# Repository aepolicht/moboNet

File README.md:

moboNet
=======

  This repo is a collection of elements contributing to one home automation project. It consists of analysis, schematics,
and software.

Notes
=====

Version 0.0.1
	Added Features:
		-Recall previous state from memory using EEPROM

	Bug Fixes:
		-Remove Flashes when receiving message

Version 0.0.2
	Added Features:
		-All communication now shall be over UDP packets

Version 0.0.3
	Changes:
		-Added notifications features to all devices
		-Added basic music detection and visualization code
			-Changes were also made to the hardware side of the music detection.
			 The low pass filter desired seems to have a cutoff right at 220 Hz.
		 	 Ideally this simple filter will consist of a 1 uF capacitor and a
		 	 7.5 kOhm resistor.
		-Implemented serial connection to bulb array to communicate with display 
		 projection from PC. Currently it checks serial, then homenet for any input
		 but if this proves to slow down the projection too much i may need a blocking
		 version where when serial is inbound all other code is ignored.
		-Changed to "FastSPI" library for communication with WS2801 LED strings
			-Also tried out an Adafruit library for this purpose but i found that
			 that library was blocking and took significantly more time to run
			 than the FastSPI library took.
			-FastSPI is non-blocking and takes around 300 uS to finish its write
		     otherwise overwriting while in progress produces undesirable effects.
	    -Implemented notifications for door knock however the whole system needs an
	     overhaul to simplify the process of [alarm device]->[base station]->[bulb clients]
	    -Implemented code for the door knock detector notifier.
	    
Version 0.0.4
	Note:
		I have begun to implement the music detection system. The basis for the whole system
		is contingent upon the frequency response of the low pass filter. I have chosen a simple
		filter with passband edge around 300 Hz. In this design a large gap between the passband 
		and the stop-band is desired because of how i plan to implement the software side of the
		music detection. Here is a rough graph of the frequency response:

			                    |H(w)| for LPF (1st order fc = 300Hz)
					  (dB)
					 0	|x x x x x x x x x x x 
					 	|                      x 
					-5	|                        x 
						|                          x
					-10	|                            x
						|                              x              
					-15	|                                x               
						|                                  x         
					-20	|                                    x           
						|                                      x         
					-25	|                                        x            
						|                                          x              
					-30	|                                            x                  
						|                                              x      
					-35	|                                                x      
						-------|----------|-----------|------------|----- Hz (log)
						0     10         100        1000         10000   

		The basis for the software side is having an understanding of the filters response
		and using this to determine whether or not the input signal is a Low, Mid or High.
		I am doing it this way to avoid any additional circuitry because i want a small
		package. It is easiest to detect the beat and very low frequencies because these are
		the largest in magnitude. I want a large gap between the passband and stop-band edges
		because i want to be able to detect other frequencies at attenuated magnitudes.
		To overcome the problem of detecting loud mids as a bass and other situations, i take
		an average of the last 64 samples as a reference. Given that reference the respective
		frequencies will then be function of the average unique to those frequency bands. To
		obtain a reference i sampled the desired frequency at different volumes IE different 
		values of the variable "ave". I then applied best fit lines and use them as cutoffs
		to determine which band a sample should be classified to. The best fits i have found
		are:
 
			Lows  (0-230Hz)   Threshold = 67*log(ave-1)-10
			Mids  (230-800Hz) Threshold = 25*log(ave-1)-5
			Highs (800+Hz)    Threshold = 12*log(ave-1)-5

		It is much more difficult to detect a high with this filter because signals higher than 
		800 Hz are attenuated more severely beginning with 800 Hz at -9 dB. The other method for
		doing this type of thing would be with a ~6000 Hz lpf and performing an FFT which i will
		do to see if its viable given the constraints.

		My preliminary DFT implementation with a 128 sample input and no special windowing takes around 2.5 seconds per DFT which is much too long. When N is 32, it takes about 155 mS.
		This would mean a sampling rate of T > 155 mS which a sampling frequency of less than
		6 Hz which is pretty much useless. The to attain a Nyquist frequency of a signal of 2000 Hz
		i need to have a sampling frequency of 4000 Hz which means the DFT finish in <250 uS. I 
		have found an FFT library for Arduino but it takes more than 600 uS to complete the FFT.
		This means i will continue with my previous method of implementing the lump spectral
		analysis.

TBD:
x-Add days support to android
x-Redesign notifications so that they are handled by base station
o-Setup music mode on all devices
x-Setup Door knock codes for base station and knocker
o-Setup Ambiance mode
o-Fix Android save and return functionality
o-Finish C# desktop application
o-Add notification options to base station and android options menu
o-Implement Groups on all devices

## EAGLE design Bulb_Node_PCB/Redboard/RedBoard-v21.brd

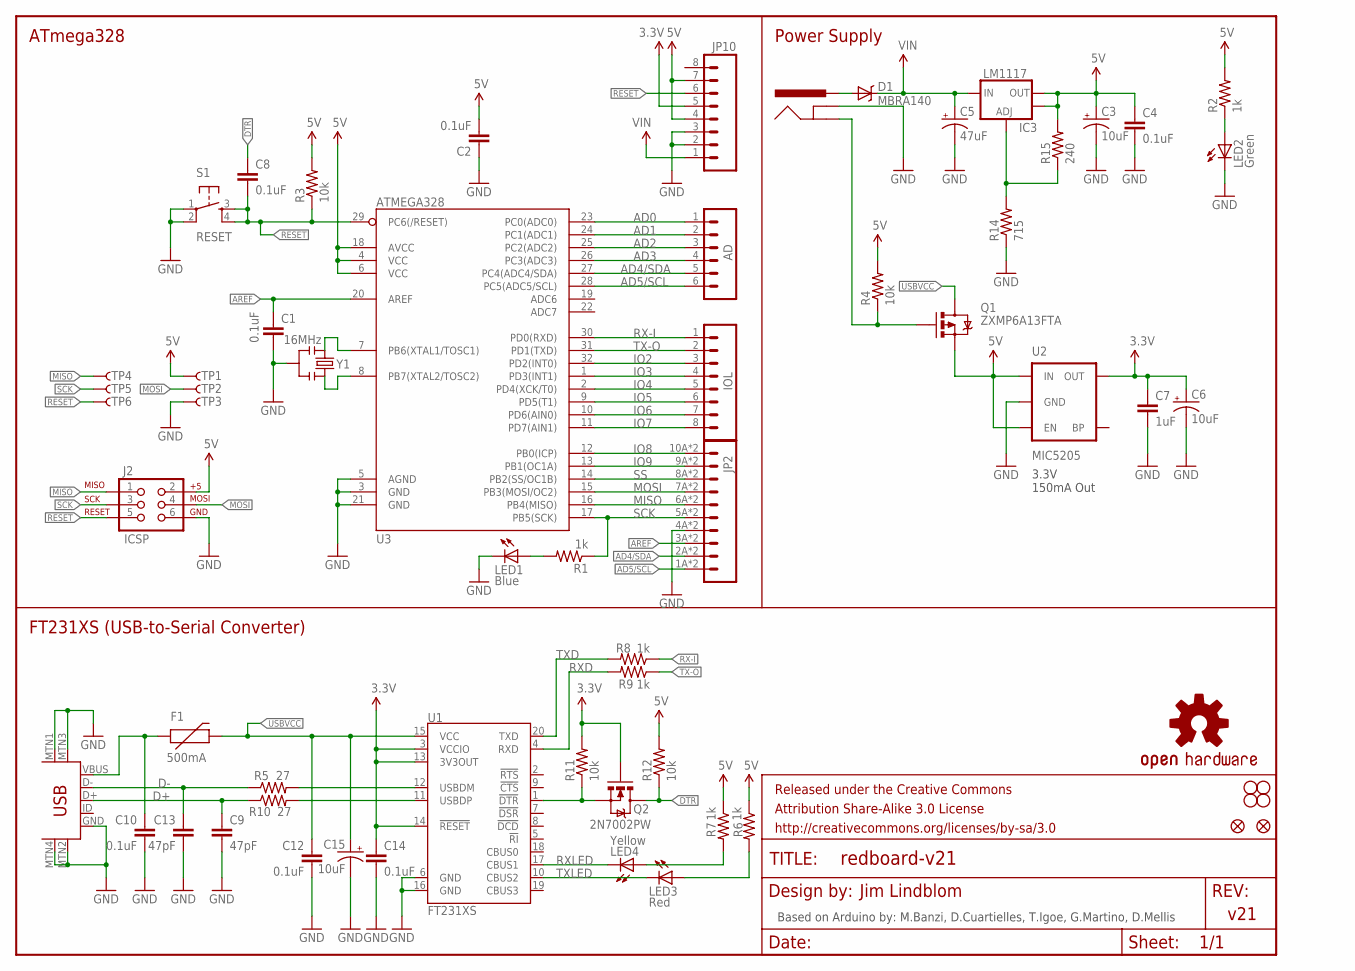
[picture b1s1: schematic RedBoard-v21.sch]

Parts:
AD: M06SMD-STRAIGHT-COMBO; 1X06_SMD_STRAIGHT_COMBO
C1, C2, C4, C8, C10, C12, C14: 0.1uF; 0603-CAP
C3, C6, C15: 10uF; EIA3216
C5: 47uF; PANASONIC_D
C7: 1uF; 0603-CAP
C9, C13: 47pF; 0603-CAP
D1: MBRA140; SMA-DIODE
F1: 500mA; PTC-1206
FRAME2: FRAME-LETTER; CREATIVE_COMMONS
IC3: LM1117; SOT223-ALT1
IOL: M08SMD-COMBO; 1X08_SMD_COMBINED
J1: POWER_JACKOVERPASTE_REDBOARD_0603; POWER_JACK_SMD_OVERPASTE_REDBOARD_0603
J2: ICSP; 2X3_SMT_POSTS
JP2: M10SMD_COMBO; 1X10_SMD_COMBINED
JP3, JP4, JP5, JP6: STAND-OFF
JP8, JP9: FIDUCIAL1X2; FIDUCIAL-1X2
JP10: M08SMD-COMBO; 1X08_SMD_COMBINED
LED1: Blue; LED-1206-NO_SILK
LED2: Green; LED-1206-NO_SILK
LED3: Red; LED-1206-NO_SILK
LED4: Yellow; LED-1206-NO_SILK
Q1: ZXMP6A13FTA; SOT23-3
Q2: 2N7002PW; SOT323
R1, R2, R6, R7, R8, R9: 1k; 0603-RES
R3, R4, R11, R12: 10k; 0603-RES
R5, R10: 27; 0603-RES
R14: 715; 0603-RES
R15: 240; 0603-RES
S1: RESET; TACTILE_SWITCH_SMD
TP1, TP2, TP3, TP4, TP5, TP6: TP-3x5; PAD.03X.05
U1: FT231XS; SSOP20_L
U2: MIC5205; SOT23-5
U3: ATMEGA328; TQFP32-08
U$13: USB-MINIB-5PIN; USB-MINIB
U$16: OSHW-LOGOS; OSHW-LOGO-S
Y1: 16MHz; RESONATOR-SMD

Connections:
3.3V: C6.A (+), C7.1, C14.1, JP10.5, Q2.1 (G), R11.2, U1.3 (VCCIO), U1.13 (3V3OUT), U1.14 (!RESET), U2.5 (OUT)
5V: C2.2, C3.A (+), C4.1, IC3.2 (OUT), IC3.4 (OUT), J2.2, JP10.4, JP10.7, Q1.2 (S), R2.2, R3.2, R4.2, R6.1, R7.1, R12.2, R15.2, TP1.P$1, U2.1 (IN), U2.3 (EN), U3.4 (VCC), U3.6 (VCC), U3.18 (AVCC)
AD0: AD.1, U3.23 (PC0(ADC0))
AD1: AD.2, U3.24 (PC1(ADC1))
AD2: AD.3, U3.25 (PC2(ADC2))
AD3: AD.4, U3.26 (PC3(ADC3))
AD4/SDA: AD.5, JP2.2A (2), JP2.2B (2), U3.27 (PC4(ADC4/SDA))
AD5/SCL: AD.6, JP2.1A (1), JP2.1B (1), U3.28 (PC5(ADC5/SCL))
AREF: C1.1, JP2.3A (3), JP2.3B (3), U3.20 (AREF)
D+: C9.1, R10.1, U$13.D+
D-: C13.1, R5.1, U$13.D-
DTR: C8.1, Q2.3 (D), R12.1
GND: C1.2, C2.1, C3.C (-), C4.2, C5.-, C6.C (-), C7.2, C9.2, C10.2, C12.2, C13.2, C14.2, C15.C (-), J1.GND (GNDBREAK), J2.6, JP2.4A (4), JP2.4B (4), JP10.2, JP10.3, LED1.C, LED2.C, R14.1, S1.1, S1.2, TP3.P$1, U1.6 (GND), U1.16 (GND), U2.2 (GND), U3.3 (GND), U3.5 (AGND), U3.21 (GND), U$13.GND, U$13.MTN1 (MTN2), U$13.MTN2 (MTN3), U$13.MTN3 (MTN1), U$13.MTN4, Y1.2
INSERT: J1.P$4 (GND), Q1.1 (G), R4.1
IO2: IOL.3, U3.32 (PD2(INT0))
IO3: IOL.4, U3.1 (PD3(INT1))
IO4: IOL.5, U3.2 (PD4(XCK/T0))
IO5: IOL.6, U3.9 (PD5(T1))
IO6: IOL.7, U3.10 (PD6(AIN0))
IO7: IOL.8, U3.11 (PD7(AIN1))
IO8: JP2.10A (10), JP2.10B (10), U3.12 (PB0(ICP))
IO9: JP2.9A (9), JP2.9B (9), U3.13 (PB1(OC1A))
MISO: J2.1, JP2.6A (6), JP2.6B (6), TP4.P$1, U3.16 (PB4(MISO))
MOSI: J2.4, JP2.7A (7), JP2.7B (7), TP2.P$1, U3.15 (PB3(MOSI/OC2))
unnamed: LED1.A, R1.2
unnamed: LED2.A, R2.1
unnamed: U3.7 (PB6(XTAL1/TOSC1)), Y1.1
unnamed: U3.8 (PB7(XTAL2/TOSC2)), Y1.3
unnamed: R5.2, U1.12 (USBDM)
unnamed: R10.2, U1.11 (USBDP)
unnamed: LED3.A, R6.2
unnamed: LED4.A, R7.2
unnamed: Q2.2 (S), R11.1, U1.1 (!DTR)
unnamed: IC3.1 (ADJ), R14.2, R15.1
PWRIN: D1.A, J1.VIN0 (PWR)
RESET: C8.2, J2.5, JP10.6, R3.1, S1.3, S1.4, TP6.P$1, U3.29 (PC6(/RESET))
RX-I: IOL.1, R8.1, U3.30 (PD0(RXD))
RXD: R9.2, U1.4 (RXD)
RXLED: LED4.C, U1.17 (CBUS1)
SCK: J2.3, JP2.5A (5), JP2.5B (5), R1.1, TP5.P$1, U3.17 (PB5(SCK))
SS: JP2.8A (8), JP2.8B (8), U3.14 (PB2(SS/OC1B))
TX-O: IOL.2, R9.1, U3.31 (PD1(TXD))
TXD: R8.2, U1.20 (TXD)
TXLED: LED3.C, U1.10 (CBUS2)
USBVCC: C12.1, C15.A (+), F1.2, Q1.3 (D), U1.15 (VCC)
VIN: C5.+, D1.C, IC3.3 (IN), JP10.1
VUSB: C10.1, F1.1, U$13.VBUS

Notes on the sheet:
Power Supply
ATmega328
FT231XS (USB-to-Serial Converter)
Based on Arduino by: M.Banzi, D.Cuartielles, T.Igoe, G.Martino, D.Mellis
3.3V 150mA Out
Jim Lindblom
v21

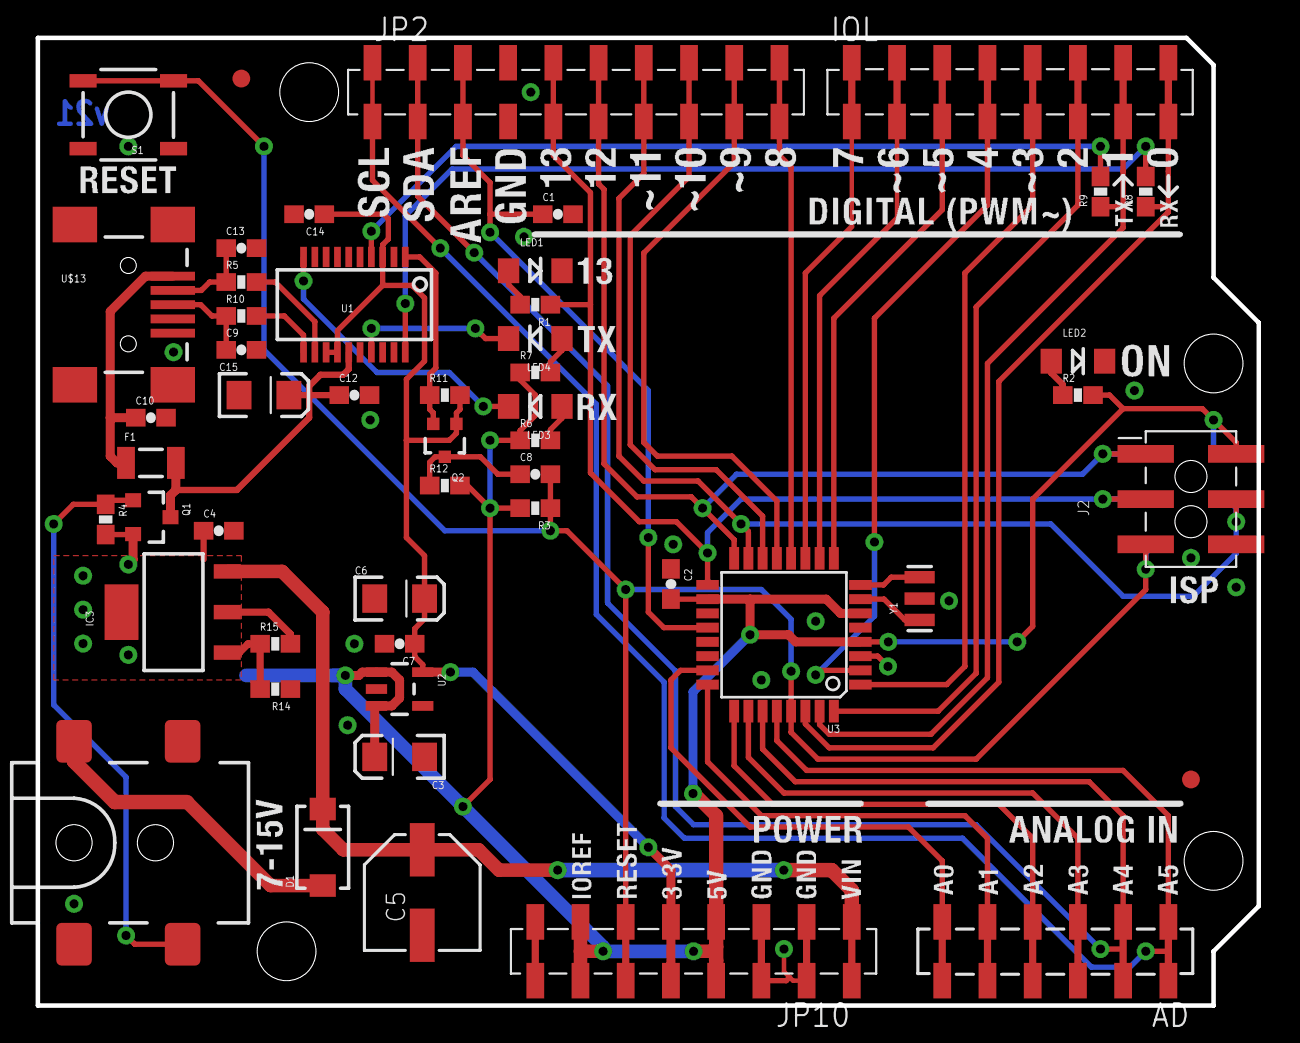
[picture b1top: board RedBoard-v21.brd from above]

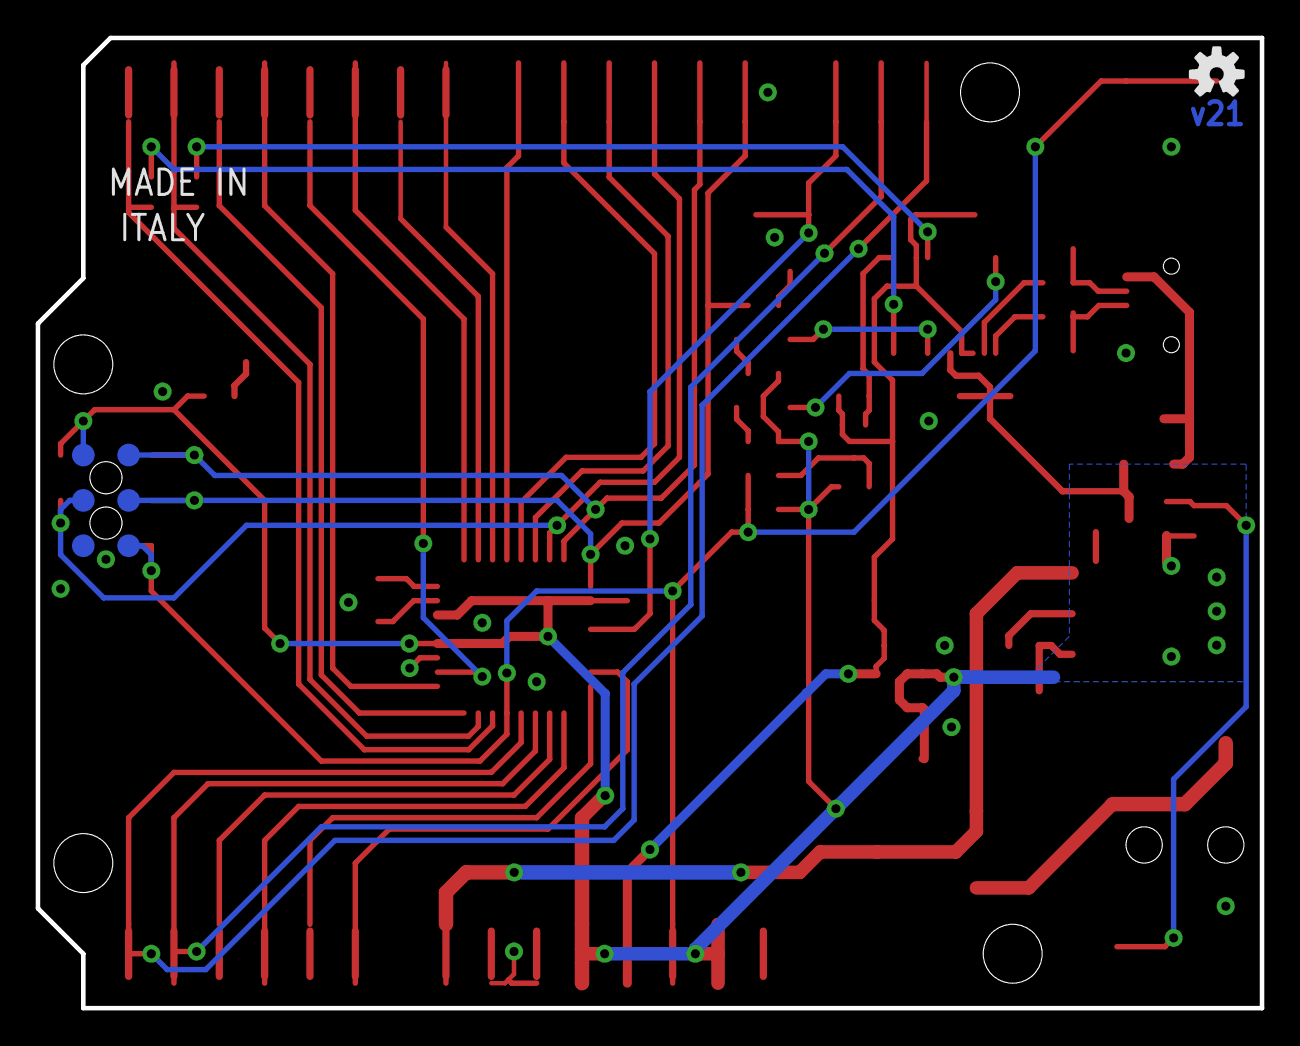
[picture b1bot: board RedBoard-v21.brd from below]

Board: 2 copper layers, 68.6 x 54.4 mm, 63 parts (7 on the bottom side), 47 nets.

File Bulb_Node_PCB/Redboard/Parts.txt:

Partlist

Exported from RedBoard-v21.sch at 2/24/2015 8:32:50 PM

EAGLE Version 7.1.0 Copyright (c) 1988-2014 CadSoft

Assembly variant: 

Part     Value                             Device                            Package                                Library               Sheet

AD                                         M06SMD-STRAIGHT-COMBO             1X06_SMD_STRAIGHT_COMBO                SparkFun              1
C1       0.1uF                             CAP0603-CAP                       0603-CAP                               SparkFun              1
C2       0.1uF                             CAP0603-CAP                       0603-CAP                               SparkFun              1
C3       10uF                              CAP_POL1206                       EIA3216                                SparkFun              1
C4       0.1uF                             CAP0603-CAP                       0603-CAP                               SparkFun              1
C5       47uF                              CAP_POLD                          PANASONIC_D                            SparkFun              1
C6       10uF                              CAP_POL1206                       EIA3216                                SparkFun              1
C7       1uF                               CAP0603-CAP                       0603-CAP                               SparkFun              1
C8       0.1uF                             CAP0603-CAP                       0603-CAP                               SparkFun              1
C9       47pF                              47PF-50V-5%(0603)                 0603-CAP                               SparkFun-Capacitors   1
C10      0.1uF                             CAP0603-CAP                       0603-CAP                               SparkFun              1
C12      0.1uF                             CAP0603-CAP                       0603-CAP                               SparkFun              1
C13      47pF                              47PF-50V-5%(0603)                 0603-CAP                               SparkFun-Capacitors   1
C14      0.1uF                             CAP0603-CAP                       0603-CAP                               SparkFun              1
C15      10uF                              CAP_POL1206                       EIA3216                                SparkFun-Capacitors   1
D1       MBRA140                           DIODE-SCHOTTKY_                   SMA-DIODE                              SparkFun              1
F1       500mA                             PTCSMD                            PTC-1206                               SparkFun              1
IC3      LM1117                            V_REG_LM1117ALT1                  SOT223-ALT1                            Testing               1
IOL                                        M08SMD-COMBO                      1X08_SMD_COMBINED                      SparkFun              1
J1       POWER_JACKOVERPASTE_REDBOARD_0603 POWER_JACKOVERPASTE_REDBOARD_0603 POWER_JACK_SMD_OVERPASTE_REDBOARD_0603 Testing               1
J2       ICSP                              AVR_SPI_PRG_6SMT_MALE             2X3_SMT_POSTS                          SparkFun-Connectors   1
JP2      M10SMD_COMBO                      M10SMD_COMBO                      1X10_SMD_COMBINED                      SparkFun-Connectors   1
JP10                                       M08SMD-COMBO                      1X08_SMD_COMBINED                      SparkFun-Connectors   1
LED1     Blue                              LED1206-NS                        LED-1206-NO_SILK                       SparkFun-LED          1
LED2     Green                             LED1206-NS                        LED-1206-NO_SILK                       SparkFun-LED          1
LED3     Red                               LED1206-NS                        LED-1206-NO_SILK                       SparkFun-LED          1
LED4     Yellow                            LED1206-NS                        LED-1206-NO_SILK                       SparkFun-LED          1
Q1       ZXMP6A13FTA                       MOSFET-PCHANNELSMD                SOT23-3                                SparkFun              1
Q2       2N7002PW                          MOSFET-NCHANNEL2N7002PW           SOT323                                 SparkFun-DiscreteSemi 1
R1       1k                                RESISTOR0603-RES                  0603-RES                               SparkFun              1
R2       1k                                RESISTOR0603-RES                  0603-RES                               SparkFun              1
R3       10k                               RESISTOR0603-RES                  0603-RES                               SparkFun              1
R4       10k                               RESISTOR0603-RES                  0603-RES                               SparkFun              1
R5       27                                RESISTOR0603-RES                  0603-RES                               SparkFun-Resistors    1
R6       1k                                RESISTOR0603-RES                  0603-RES                               SparkFun              1
R7       1k                                RESISTOR0603-RES                  0603-RES                               SparkFun              1
R8       1k                                RESISTOR0603-RES                  0603-RES                               SparkFun              1
R9       1k                                RESISTOR0603-RES                  0603-RES                               SparkFun              1
R10      27                                RESISTOR0603-RES                  0603-RES                               SparkFun-Resistors    1
R11      10k                               RESISTOR0603-RES                  0603-RES                               SparkFun              1
R12      10k                               RESISTOR0603-RES                  0603-RES                               SparkFun              1
R14      715                               RESISTOR0603-RES                  0603-RES                               SparkFun              1
R15      240                               RESISTOR0603-RES                  0603-RES                               SparkFun              1
S1       RESET                             TAC_SWITCHSMD                     TACTILE_SWITCH_SMD                     SparkFun              1
TP1      TP-3x5                            TEST-POINT3X5                     PAD.03X.05                             SparkFun-Passives     1
TP2      TP-3x5                            TEST-POINT3X5                     PAD.03X.05                             SparkFun-Passives     1
TP3      TP-3x5                            TEST-POINT3X5                     PAD.03X.05                             SparkFun-Passives     1
TP4      TP-3x5                            TEST-POINT3X5                     PAD.03X.05                             SparkFun-Passives     1
TP5      TP-3x5                            TEST-POINT3X5                     PAD.03X.05                             SparkFun-Passives     1
TP6      TP-3x5                            TEST-POINT3X5                     PAD.03X.05                             SparkFun-Passives     1
U$13     USB-MINIB-5PIN                    USB-MINIB-5PIN                    USB-MINIB                              SparkFun-Connectors   1
U1       FT231XS                           FT231XS                           SSOP20_L                               SparkFun-DigitalIC    1
U2       MIC5205                           V_REG_LDOSMD                      SOT23-5                                SparkFun              1
U3       ATMEGA328                         ATMEGA168                         TQFP32-08                              SparkFun              1
Y1       16MHz                             RESONATORSMD                      RESONATOR-SMD                          SparkFun-FreqCtrl     1

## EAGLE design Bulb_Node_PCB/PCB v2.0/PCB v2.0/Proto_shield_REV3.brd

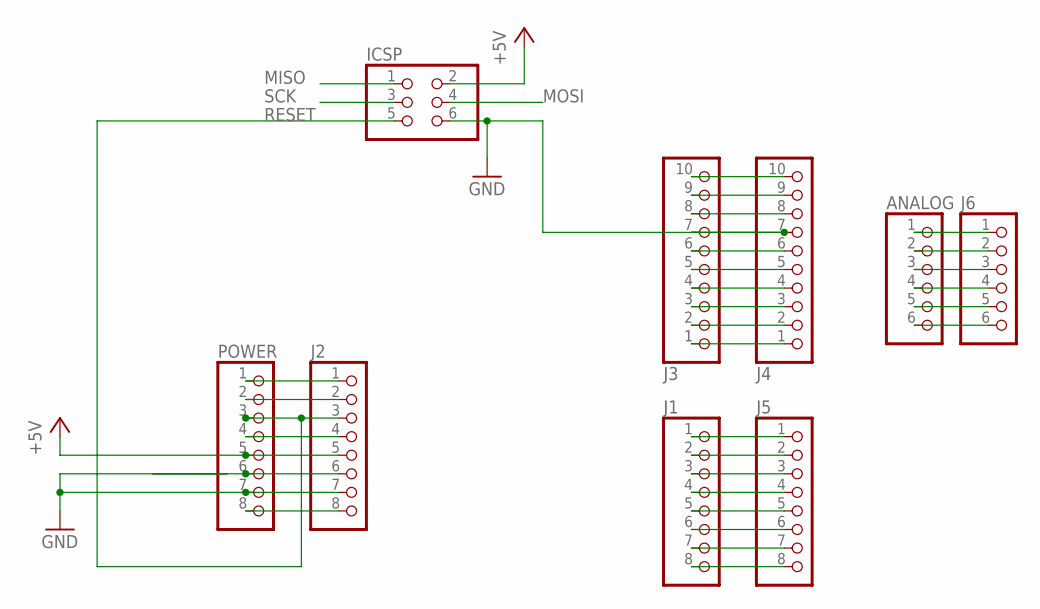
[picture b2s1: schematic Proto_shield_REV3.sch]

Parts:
ANALOG: PINHD-1X6; 1X06
ICSP: PINHD-2X3; 2X03
J1, J2, J5: PINHD-1X8TH; 1X08-TH
J3, J4: PINHD-1X10TH; 1X10-TH
J6: PINHD-1X6; 1X06
POWER: PINHD-1X8TH; 1X08-TH

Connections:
+5V: ICSP.2, J2.5, POWER.5
+9V: J2.8, POWER.8
GND: ICSP.6, J2.7, J3.7, J4.7, POWER.7
MISO: ICSP.1
MOSI: ICSP.4
unnamed: J3.6, J4.6
unnamed: J3.1, J4.1
unnamed: J3.4, J4.4
unnamed: J3.5, J4.5
unnamed: J3.2, J4.2
unnamed: J3.3, J4.3
unnamed: J1.1, J5.1
unnamed: J1.2, J5.2
unnamed: J1.3, J5.3
unnamed: J1.4, J5.4
unnamed: J1.5, J5.5
unnamed: J1.6, J5.6
unnamed: J1.7, J5.7
unnamed: J1.8, J5.8
unnamed: ANALOG.1, J6.1
unnamed: ANALOG.2, J6.2
unnamed: ANALOG.3, J6.3
unnamed: ANALOG.4, J6.4
unnamed: ANALOG.5, J6.5
unnamed: ANALOG.6, J6.6
unnamed: J2.6, POWER.6
unnamed: J2.2, POWER.2
unnamed: J2.1, POWER.1
unnamed: J3.9, J4.9
unnamed: J3.10, J4.10
unnamed: J3.8, J4.8
unnamed: J2.4, POWER.4
RESET: ICSP.5, J2.3, POWER.3
SCK: ICSP.3

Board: 2 copper layers, 9 parts (0 on the bottom side), 31 nets, no tracks yet.

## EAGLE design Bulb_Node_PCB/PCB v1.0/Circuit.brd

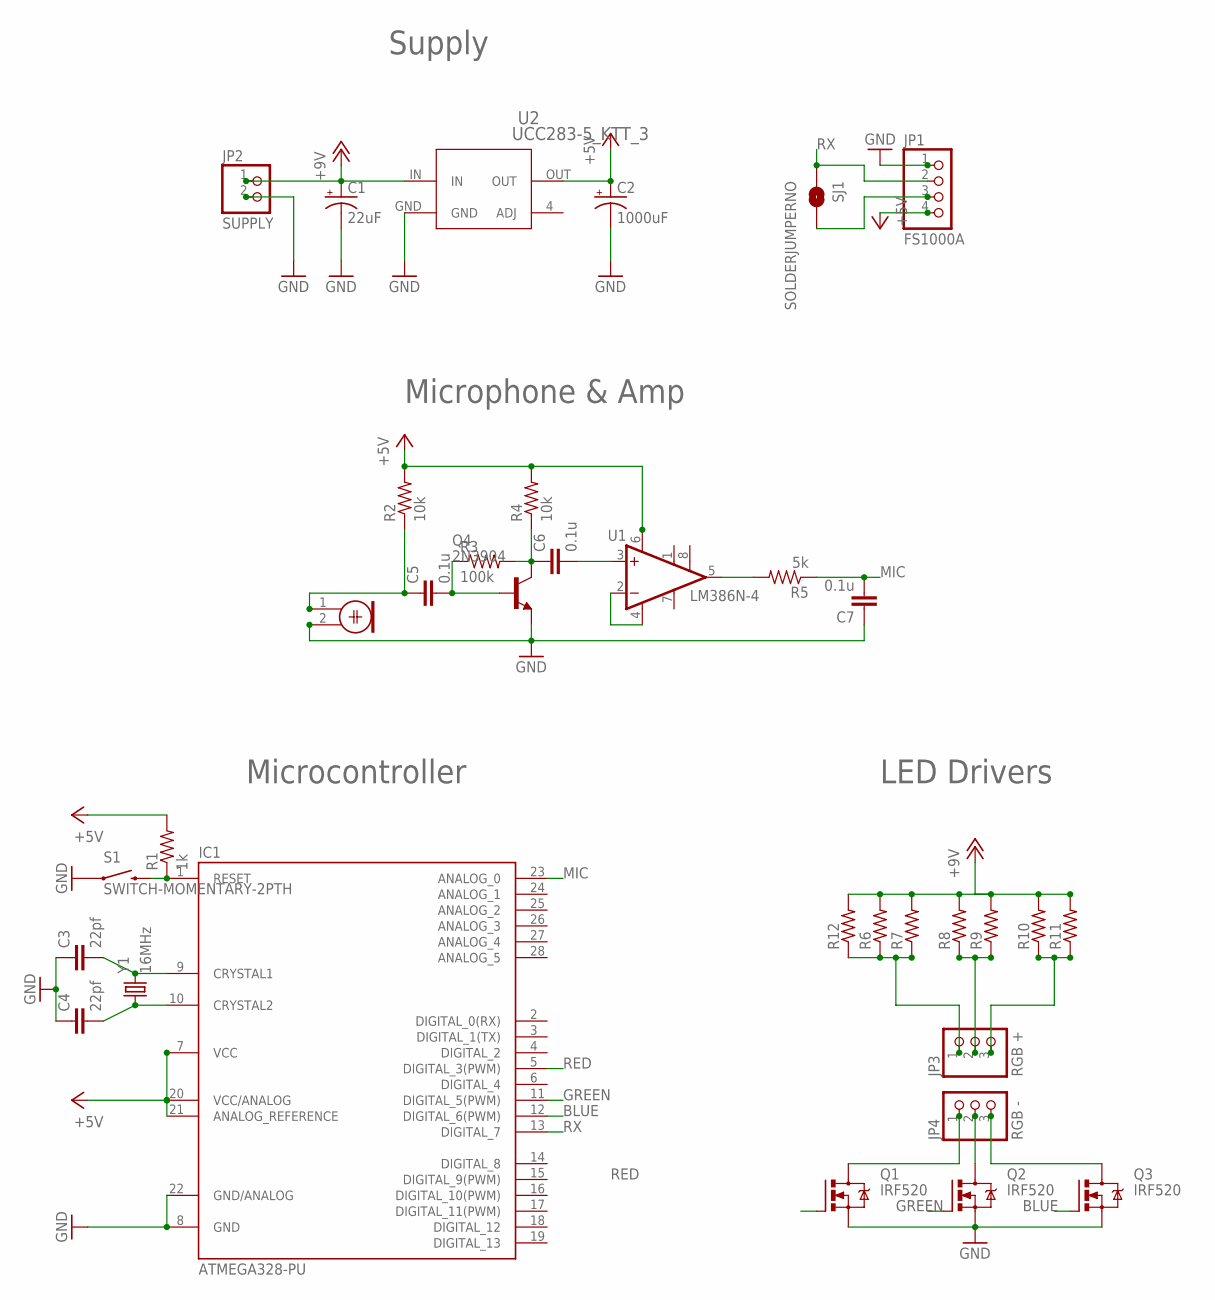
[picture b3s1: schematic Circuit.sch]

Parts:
C1: 22uF; CPOL-RADIAL-10UF-25V
C2: 1000uF; CPOL-RADIAL-1000UF-25V
C3, C4: 22pf; CAP-PTH-SMALL-KIT
C5, C6, C7: 0.1u; CAP-PTH-5MM
IC1: ATMEGA328-PU; DIL28-3
JP1: FS1000A; 1X04
JP2: SUPPLY; 1X02
JP3: RGB +; 1X03
JP4: RGB -; 1X03
M1: MIC; WM-62PC/62PK
Q1, Q2, Q3: IRF520; TO220BV
Q4: 2N3904; TO92
R1: 1k; AXIAL-0.3EZ
R2, R4: 10k; AXIAL-0.3EZ
R3: 100k; AXIAL-0.3EZ
R5: 5k; AXIAL-0.3EZ
R6, R7, R8, R9, R10, R11, R12: R-US_0613/5V; P0613V
S1: SWITCH-MOMENTARY-2PTH; TACTILE-PTH
SJ1: SOLDERJUMPERNO; SJ_2S-NO
U1: LM386N-4; DIL08
U2: UCC283-5_KTT_3; KTT3_6P22X6P6
Y1: 16MHz; HC49US

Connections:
+5V: C2.1 (+), IC1.7 (VCC), IC1.20 (VCC/ANALOG), IC1.21 (ANALOG_REFERENCE), JP1.4, R1.P$2 (2), R2.P$2 (2), R4.P$2 (2), U1.6 (VS), U2.OUT
+12V: C1.1 (+), JP2.1, R6.2, R7.2, R8.2, R9.2, R10.2, R11.2, R12.2, U2.IN
BLUE: IC1.12 (DIGITAL_6(PWM)), Q3.G
GND: C1.2 (-), C2.2 (-), C3.1, C4.1, C7.1, IC1.8 (GND), IC1.22 (GND/ANALOG), JP1.1, JP2.2, M1.2, Q1.S, Q2.S, Q3.S, Q4.3 (E), S1.1, U2.GND
GREEN: IC1.11 (DIGITAL_5(PWM)), Q2.G
MIC: C7.2, IC1.23 (ANALOG_0), R5.P$1 (1)
unnamed: JP1.3, SJ1.2
unnamed: C3.2, IC1.9 (CRYSTAL1), Y1.2
unnamed: C4.2, IC1.10 (CRYSTAL2), Y1.1
unnamed: IC1.1 (RESET), R1.P$1 (1), S1.3 (2)
unnamed: JP4.1, Q1.D
unnamed: JP4.2, Q2.D
unnamed: JP4.3, Q3.D
unnamed: C5.2, Q4.2 (B), R3.P$1 (1)
unnamed: C5.1, M1.1, R2.P$1 (1)
unnamed: C6.1, Q4.1 (C), R3.P$2 (2), R4.P$1 (1)
unnamed: R5.P$2 (2), U1.5 (OUT)
unnamed: U1.2 (-IN), U1.4 (GND)
unnamed: JP3.1, R6.1, R7.1, R12.1
unnamed: JP3.2, R8.1, R9.1
unnamed: JP3.3, R10.1, R11.1
unnamed: C6.2, U1.3 (+IN)
RED: IC1.5 (DIGITAL_3(PWM)), Q1.G
RX: IC1.13 (DIGITAL_7), JP1.2, SJ1.1

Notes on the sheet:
Microcontroller
LED Drivers
Microphone & Amp
Supply

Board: 2 copper layers, 34 parts (0 on the bottom side), 24 nets, no tracks yet.

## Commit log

2018-02-20 :circus_tent: Added .gitattributes & .gitignore files

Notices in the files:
parts and their libraries:
SparkFun-FreqCtrl: Licensing: CC v3.0 Share-Alike You are welcome to use this library for commercial purposes.
SparkFun-Aesthetics: Released under the Creative Commons Attribution Share-Alike 3.0 License
SparkFun-Aesthetics: http://creativecommons.org/licenses/by-sa/3.0
